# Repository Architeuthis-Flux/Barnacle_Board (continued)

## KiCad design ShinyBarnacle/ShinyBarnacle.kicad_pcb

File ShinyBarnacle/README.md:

# Shiny Barnacle

This one doesn't connect to the breadboard rows, just the RGBs. It mounts as a USB drive so you can drop a text file with colors to light the rows (or give it a sequence to step you through building a circuit.)

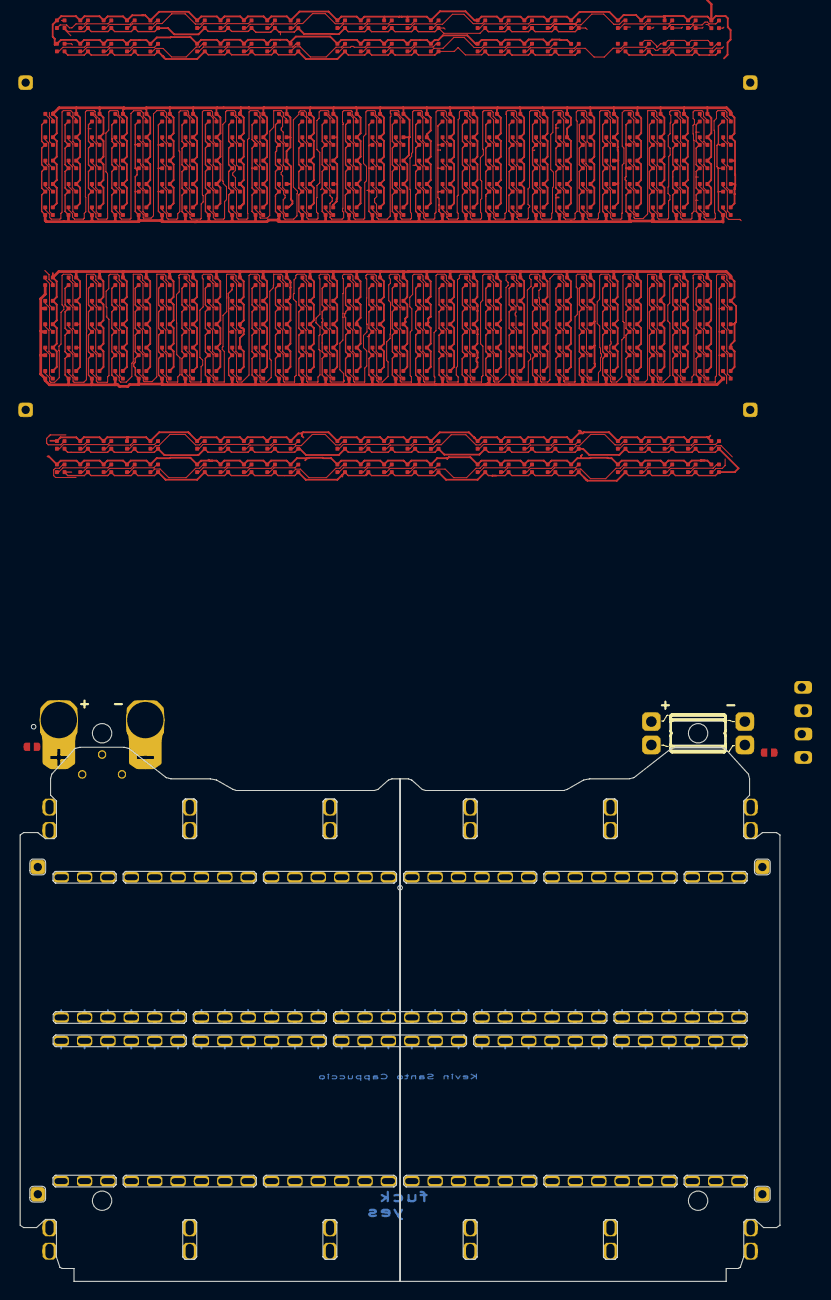
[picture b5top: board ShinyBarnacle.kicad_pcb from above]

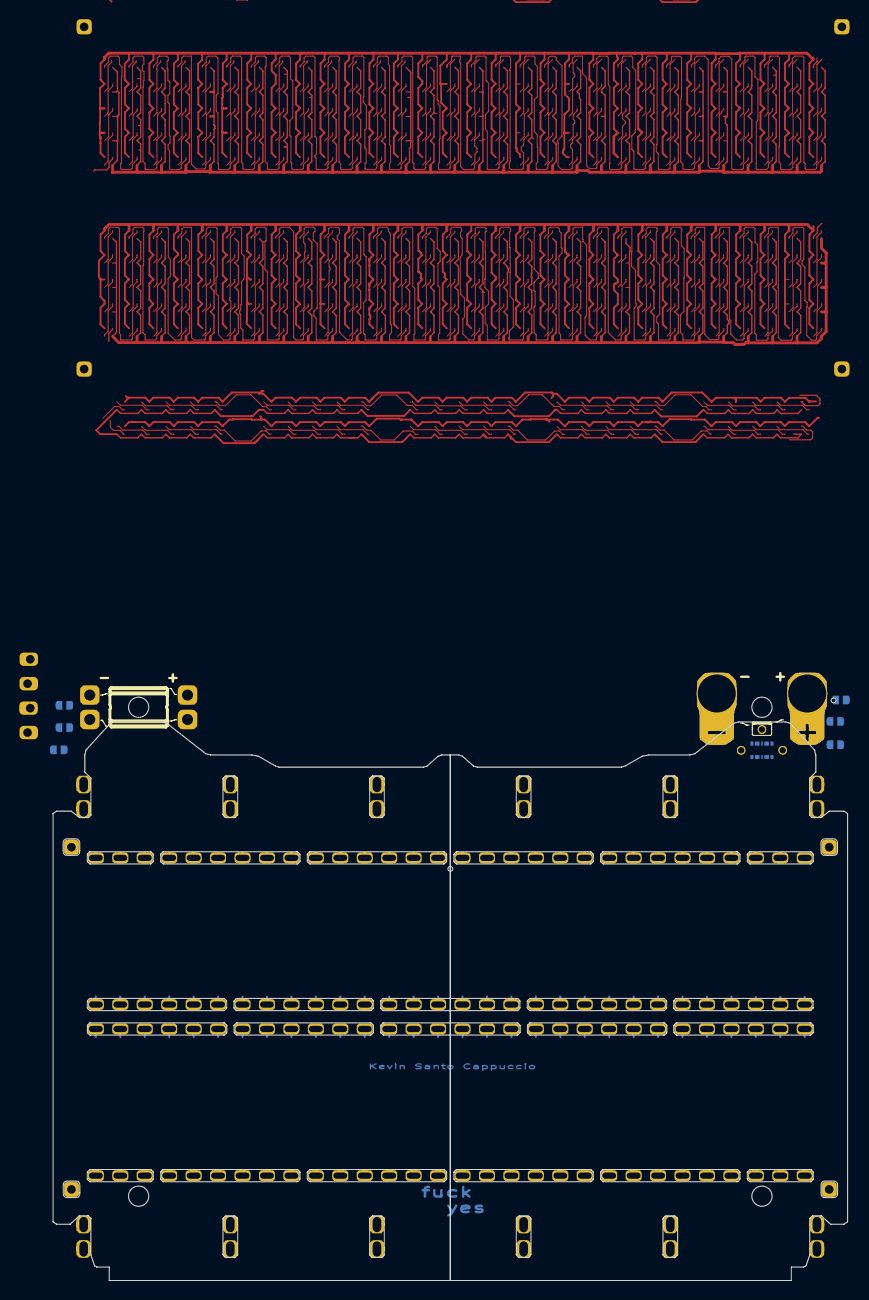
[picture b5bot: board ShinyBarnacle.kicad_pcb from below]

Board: 2 copper layers, 82.6 x 58.0 mm, 429 parts (9 on the bottom side), 409 nets.

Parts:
D1011, D1012, D1013, D1014, D1015, D1021, D1022, D1023, D1024, D1025, D1031, D1032, D1033, D1034, D1035, D1041, D1042, D1043, D1044, D1045, D1051, D1052, D1053, D1054, D1055, D1061, D1062, D1063, D1064, D1065, D1071, D1072, D1073, D1074, D1075, D1081, D1082, D1083, D1084, D1085, D1091, D1092, D1093, D1094, D1095, D1101, D1102, D1103, D1104, D1105, D1111, D1112, D1113, D1114, D1115, D1121, D1122, D1123, D1124, D1125, D1131, D1132, D1133, D1134, D1135, D1141, D1142, D1143, D1144, D1145, D1151, D1152, D1153, D1154, D1155, D1161, D1162, D1163, D1164, D1165, D1171, D1172, D1173, D1174, D1175, D1181, D1182, D1183, D1184, D1185, D1191, D1192, D1193, D1194, D1195, D1201, D1202, D1203, D1204, D1205, D1211, D1212, D1213, D1214, D1215, D1221, D1222, D1223, D1224, D1225, D1231, D1232, D1233, D1234, D1235, D1241, D1242, D1243, D1244, D1245, D1251, D1252, D1253, D1254, D1255, D1261, D1262, D1263, D1264, D1265, D1271, D1272, D1273, D1274, D1275, D1281, D1282, D1283, D1284, D1285, D1291, D1292, D1293, D1294, D1295, D1301, D1302, D1303, D1304, D1305, D1311, D1312, D1313, D1314, D1315, D1321, D1322, D1323, D1324, D1325, D1331, D1332, D1333, D1334, D1335, D1341, D1342, D1343, D1344, D1345, D1351, D1352, D1353, D1354, D1355, D1361, D1362, D1363, D1364, D1365, D1371, D1372, D1373, D1374, D1375, D1381, D1382, D1383, D1384, D1385, D1391, D1392, D1393, D1394, D1395, D1401, D1402, D1403, D1404, D1405, D1411, D1412, D1413, D1414, D1415, D1421, D1422, D1423, D1424, D1425, D1431, D1432, D1433, D1434, D1435, D1441, D1442, D1443, D1444, D1445, D1451, D1452, D1453, D1454, D1455, D1461, D1462, D1463, D1464, D1465, D1471, D1472, D1473, D1474, D1475, D1481, D1482, D1483, D1484, D1485, D1491, D1492, D1493, D1494, D1495, D1501, D1502, D1503, D1504, D1505, D1511, D1512, D1513, D1514, D1515, D1521, D1522, D1523, D1524, D1525, D1531, D1532, D1533, D1534, D1535, D1541, D1542, D1543, D1544, D1545, D1551, D1552, D1553, D1554, D1555, D1561, D1562, D1563, D1564, D1565, D1571, D1572, D1573, D1574, D1575, D1581, D1582, D1583, D1584, D1585, D1591, D1592, D1593, D1594, D1595, D1601, D1602, D1603, D1604, D1605, D1611, D1612, D1613, D1614, D1615, D1616, D1617, D1618, D1619, D1620, D1621, D1622, D1623, D1624, D1625, D1626, D1627, D1628, D1629, D1630, D1631, D1632, D1633, D1634, D1635, D1636, D1637, D1638, D1639, D1640, D1641, D1642, D1643, D1644, D1645, D1646, D1647, D1648, D1649, D1650, D1651, D1652, D1653, D1654, D1655, D1656, D1657, D1658, D1659, D1660, D1711, D1712, D1713, D1714, D1715, D1716, D1717, D1718, D1719, D1720, D1721, D1722, D1723, D1724, D1725, D1726, D1727, D1728, D1729, D1730, D1731, D1732, D1733, D1734, D1735, D1736, D1737, D1738, D1739, D1740, D1741, D1742, D1743, D1744, D1745, D1746, D1747, D1748, D1749, D1750, D1751, D1752, D1753, D1754, D1755, D1756, D1757, D1758, D1759, D1760: WS2812B; XL-1010RGBC-WS2812B
J1, J1#2: Conn_02x35_Top_Bottom; HEE70LP03BK_NumberedPads_CardGuide
J2: pad_sense_1; PinHeader_1x1_Smaller
J3: pad_sense_30; PinHeader_1x1_Smaller
J4: pad_sense_60; PinHeader_1x1_Smaller
J5: pad_sense_31; PinHeader_1x1_Smaller
J11: Connector_Breadboard; Breadboard_CustomClips_CorrectPins_2
J11#2: TopOutMAIN; PinHeader_1x1_Smaller
J12: TopInMAIN; PinHeader_1x1_Smaller
J13: BottomInMAIN; PinHeader_1x1_Smaller
J14: Conn_01x06; GT-B0353FSV06-02B0201
J15: BottomOutMAIN; PinHeader_1x1_Smaller
JP3, JP4, JP5, JP6, JP7, JP8, JP9, JP10: SolderJumper_2_Open; SolderJumper_2_Open_Small
TP16: LED DIN; PinHeader_1x1_0.6mm_tinyAF
TP18: LED 5V; PinHeader_1x1_0.6mm_tinyAF
TP19: LED GND; PinHeader_1x1_0.6mm_tinyAF
TP24: TOP_POS_RAIL; Pad_Clip_Banana_PlusSmaller_topBottom
TP25: TOP_POS_RAIL; PINHEADER_Larger_Pad
TP26: TOP_NEG_RAIL; Pad_Clip_Banana_MinusSmaller_topBottom
TP27: TOP_NEG_RAIL; PINHEADER_Larger_Pad
TP29: BOTTOM_POS_RAIL; PINHEADER_Larger_Pad
TP31: BOTTOM_NEG_RAIL; PINHEADER_Larger_Pad

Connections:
+5V: D1011.2 (VDD), D1012.2 (VDD), D1013.2 (VDD), D1014.2 (VDD), D1015.2 (VDD), D1021.2 (VDD), D1022.2 (VDD), D1023.2 (VDD), D1024.2 (VDD), D1025.2 (VDD), D1031.2 (VDD), D1032.2 (VDD), D1033.2 (VDD), D1034.2 (VDD), D1035.2 (VDD), D1041.2 (VDD), D1042.2 (VDD), D1043.2 (VDD), D1044.2 (VDD), D1045.2 (VDD), D1051.2 (VDD), D1052.2 (VDD), D1053.2 (VDD), D1054.2 (VDD), D1055.2 (VDD), D1061.2 (VDD), D1062.2 (VDD), D1063.2 (VDD), D1064.2 (VDD), D1065.2 (VDD), D1071.2 (VDD), D1072.2 (VDD), D1073.2 (VDD), D1074.2 (VDD), D1075.2 (VDD), D1081.2 (VDD), D1082.2 (VDD), D1083.2 (VDD), D1084.2 (VDD), D1085.2 (VDD), D1091.2 (VDD), D1092.2 (VDD), D1093.2 (VDD), D1094.2 (VDD), D1095.2 (VDD), D1101.2 (VDD), D1102.2 (VDD), D1103.2 (VDD), D1104.2 (VDD), D1105.2 (VDD), D1111.2 (VDD), D1112.2 (VDD), D1113.2 (VDD), D1114.2 (VDD), D1115.2 (VDD), D1121.2 (VDD), D1122.2 (VDD), D1123.2 (VDD), D1124.2 (VDD), D1125.2 (VDD), D1131.2 (VDD), D1132.2 (VDD), D1133.2 (VDD), D1134.2 (VDD), D1135.2 (VDD), D1141.2 (VDD), D1142.2 (VDD), D1143.2 (VDD), D1144.2 (VDD), D1145.2 (VDD), D1151.2 (VDD), D1152.2 (VDD), D1153.2 (VDD), D1154.2 (VDD), D1155.2 (VDD), D1161.2 (VDD), D1162.2 (VDD), D1163.2 (VDD), D1164.2 (VDD), D1165.2 (VDD), D1171.2 (VDD), D1172.2 (VDD), D1173.2 (VDD), D1174.2 (VDD), D1175.2 (VDD), D1181.2 (VDD), D1182.2 (VDD), D1183.2 (VDD), D1184.2 (VDD), D1185.2 (VDD), D1191.2 (VDD), D1192.2 (VDD), D1193.2 (VDD), D1194.2 (VDD), D1195.2 (VDD), D1201.2 (VDD), D1202.2 (VDD), D1203.2 (VDD), D1204.2 (VDD), D1205.2 (VDD), D1211.2 (VDD), D1212.2 (VDD), D1213.2 (VDD), D1214.2 (VDD), D1215.2 (VDD), D1221.2 (VDD), D1222.2 (VDD), D1223.2 (VDD), D1224.2 (VDD), D1225.2 (VDD), D1231.2 (VDD), D1232.2 (VDD), D1233.2 (VDD), D1234.2 (VDD), D1235.2 (VDD), D1241.2 (VDD), D1242.2 (VDD), D1243.2 (VDD), D1244.2 (VDD), D1245.2 (VDD), D1251.2 (VDD), D1252.2 (VDD), D1253.2 (VDD), D1254.2 (VDD), D1255.2 (VDD), D1261.2 (VDD), D1262.2 (VDD), D1263.2 (VDD), D1264.2 (VDD), D1265.2 (VDD), D1271.2 (VDD), D1272.2 (VDD), D1273.2 (VDD), D1274.2 (VDD), D1275.2 (VDD), D1281.2 (VDD), D1282.2 (VDD), D1283.2 (VDD), D1284.2 (VDD), D1285.2 (VDD), D1291.2 (VDD), D1292.2 (VDD), D1293.2 (VDD), D1294.2 (VDD), D1295.2 (VDD), D1301.2 (VDD), D1302.2 (VDD), D1303.2 (VDD), D1304.2 (VDD), D1305.2 (VDD), D1311.2 (VDD), D1312.2 (VDD), D1313.2 (VDD), D1314.2 (VDD), D1315.2 (VDD), D1321.2 (VDD), D1322.2 (VDD), D1323.2 (VDD), D1324.2 (VDD), D1325.2 (VDD), D1331.2 (VDD), D1332.2 (VDD), D1333.2 (VDD), D1334.2 (VDD), D1335.2 (VDD), D1341.2 (VDD), D1342.2 (VDD), D1343.2 (VDD), D1344.2 (VDD), D1345.2 (VDD), D1351.2 (VDD), D1352.2 (VDD), D1353.2 (VDD), D1354.2 (VDD), D1355.2 (VDD), D1361.2 (VDD), D1362.2 (VDD), D1363.2 (VDD), D1364.2 (VDD), D1365.2 (VDD), D1371.2 (VDD), D1372.2 (VDD), D1373.2 (VDD), D1374.2 (VDD), D1375.2 (VDD), D1381.2 (VDD), D1382.2 (VDD), D1383.2 (VDD), D1384.2 (VDD), D1385.2 (VDD), D1391.2 (VDD), D1392.2 (VDD), D1393.2 (VDD), D1394.2 (VDD), D1395.2 (VDD), D1401.2 (VDD), D1402.2 (VDD), D1403.2 (VDD), D1404.2 (VDD), D1405.2 (VDD), D1411.2 (VDD), D1412.2 (VDD), D1413.2 (VDD), D1414.2 (VDD), D1415.2 (VDD), D1421.2 (VDD), D1422.2 (VDD), D1423.2 (VDD), D1424.2 (VDD), D1425.2 (VDD), D1431.2 (VDD), D1432.2 (VDD), D1433.2 (VDD), D1434.2 (VDD), D1435.2 (VDD), D1441.2 (VDD), D1442.2 (VDD), D1443.2 (VDD), D1444.2 (VDD), D1445.2 (VDD), D1451.2 (VDD), D1452.2 (VDD), D1453.2 (VDD), D1454.2 (VDD), D1455.2 (VDD), D1461.2 (VDD), D1462.2 (VDD), D1463.2 (VDD), D1464.2 (VDD), D1465.2 (VDD), D1471.2 (VDD), D1472.2 (VDD), D1473.2 (VDD), D1474.2 (VDD), D1475.2 (VDD), D1481.2 (VDD), D1482.2 (VDD), D1483.2 (VDD), D1484.2 (VDD), D1485.2 (VDD), D1491.2 (VDD), D1492.2 (VDD), D1493.2 (VDD), D1494.2 (VDD), D1495.2 (VDD), D1501.2 (VDD), D1502.2 (VDD), D1503.2 (VDD), D1504.2 (VDD), D1505.2 (VDD), D1511.2 (VDD), D1512.2 (VDD), D1513.2 (VDD), D1514.2 (VDD), D1515.2 (VDD), D1521.2 (VDD), D1522.2 (VDD), D1523.2 (VDD), D1524.2 (VDD), D1525.2 (VDD), D1531.2 (VDD), D1532.2 (VDD), D1533.2 (VDD), D1534.2 (VDD), D1535.2 (VDD), D1541.2 (VDD), D1542.2 (VDD), D1543.2 (VDD), D1544.2 (VDD), D1545.2 (VDD), D1551.2 (VDD), D1552.2 (VDD), D1553.2 (VDD), D1554.2 (VDD), D1555.2 (VDD), D1561.2 (VDD), D1562.2 (VDD), D1563.2 (VDD), D1564.2 (VDD), D1565.2 (VDD), D1571.2 (VDD), D1572.2 (VDD), D1573.2 (VDD), D1574.2 (VDD), D1575.2 (VDD), D1581.2 (VDD), D1582.2 (VDD), D1583.2 (VDD), D1584.2 (VDD), D1585.2 (VDD), D1591.2 (VDD), D1592.2 (VDD), D1593.2 (VDD), D1594.2 (VDD), D1595.2 (VDD), D1601.2 (VDD), D1602.2 (VDD), D1603.2 (VDD), D1604.2 (VDD), D1605.2 (VDD), D1611.2 (VDD), D1612.2 (VDD), D1613.2 (VDD), D1614.2 (VDD), D1615.2 (VDD), D1616.2 (VDD), D1617.2 (VDD), D1618.2 (VDD), D1619.2 (VDD), D1620.2 (VDD), D1621.2 (VDD), D1622.2 (VDD), D1623.2 (VDD), D1624.2 (VDD), D1625.2 (VDD), D1626.2 (VDD), D1627.2 (VDD), D1628.2 (VDD), D1629.2 (VDD), D1630.2 (VDD), D1631.2 (VDD), D1632.2 (VDD), D1633.2 (VDD), D1634.2 (VDD), D1635.2 (VDD), D1636.2 (VDD), D1637.2 (VDD), D1638.2 (VDD), D1639.2 (VDD), D1640.2 (VDD), D1641.2 (VDD), D1642.2 (VDD), D1643.2 (VDD), D1644.2 (VDD), D1645.2 (VDD), D1646.2 (VDD), D1647.2 (VDD), D1648.2 (VDD), D1649.2 (VDD), D1650.2 (VDD), D1651.2 (VDD), D1652.2 (VDD), D1653.2 (VDD), D1654.2 (VDD), D1655.2 (VDD), D1656.2 (VDD), D1657.2 (VDD), D1658.2 (VDD), D1659.2 (VDD), D1660.2 (VDD), D1711.2 (VDD), D1712.2 (VDD), D1713.2 (VDD), D1714.2 (VDD), D1715.2 (VDD), D1716.2 (VDD), D1717.2 (VDD), D1718.2 (VDD), D1719.2 (VDD), D1720.2 (VDD), D1721.2 (VDD), D1722.2 (VDD), D1723.2 (VDD), D1724.2 (VDD), D1725.2 (VDD), D1726.2 (VDD), D1727.2 (VDD), D1728.2 (VDD), D1729.2 (VDD), D1730.2 (VDD), D1731.2 (VDD), D1732.2 (VDD), D1733.2 (VDD), D1734.2 (VDD), D1735.2 (VDD), D1736.2 (VDD), D1737.2 (VDD), D1738.2 (VDD), D1739.2 (VDD), D1740.2 (VDD), D1741.2 (VDD), D1742.2 (VDD), D1743.2 (VDD), D1744.2 (VDD), D1745.2 (VDD), D1746.2 (VDD), D1747.2 (VDD), D1748.2 (VDD), D1749.2 (VDD), D1750.2 (VDD), D1751.2 (VDD), D1752.2 (VDD), D1753.2 (VDD), D1754.2 (VDD), D1755.2 (VDD), D1756.2 (VDD), D1757.2 (VDD), D1758.2 (VDD), D1759.2 (VDD), D1760.2 (VDD)
BOT_RAIL_NEG: J11.64 (Bot_Neg), JP4.2 (B), JP8.2 (B), TP31.1
BOT_RAIL_POS: J11.63 (Bot_Pos), JP5.2 (B), JP9.2 (B), TP29.1
GND: D1011.3 (VSS), D1012.3 (VSS), D1013.3 (VSS), D1014.3 (VSS), D1015.3 (VSS), D1021.3 (VSS), D1022.3 (VSS), D1023.3 (VSS), D1024.3 (VSS), D1025.3 (VSS), D1031.3 (VSS), D1032.3 (VSS), D1033.3 (VSS), D1034.3 (VSS), D1035.3 (VSS), D1041.3 (VSS), D1042.3 (VSS), D1043.3 (VSS), D1044.3 (VSS), D1045.3 (VSS), D1051.3 (VSS), D1052.3 (VSS), D1053.3 (VSS), D1054.3 (VSS), D1055.3 (VSS), D1061.3 (VSS), D1062.3 (VSS), D1063.3 (VSS), D1064.3 (VSS), D1065.3 (VSS), D1071.3 (VSS), D1072.3 (VSS), D1073.3 (VSS), D1074.3 (VSS), D1075.3 (VSS), D1081.3 (VSS), D1082.3 (VSS), D1083.3 (VSS), D1084.3 (VSS), D1085.3 (VSS), D1091.3 (VSS), D1092.3 (VSS), D1093.3 (VSS), D1094.3 (VSS), D1095.3 (VSS), D1101.3 (VSS), D1102.3 (VSS), D1103.3 (VSS), D1104.3 (VSS), D1105.3 (VSS), D1111.3 (VSS), D1112.3 (VSS), D1113.3 (VSS), D1114.3 (VSS), D1115.3 (VSS), D1121.3 (VSS), D1122.3 (VSS), D1123.3 (VSS), D1124.3 (VSS), D1125.3 (VSS), D1131.3 (VSS), D1132.3 (VSS), D1133.3 (VSS), D1134.3 (VSS), D1135.3 (VSS), D1141.3 (VSS), D1142.3 (VSS), D1143.3 (VSS), D1144.3 (VSS), D1145.3 (VSS), D1151.3 (VSS), D1152.3 (VSS), D1153.3 (VSS), D1154.3 (VSS), D1155.3 (VSS), D1161.3 (VSS), D1162.3 (VSS), D1163.3 (VSS), D1164.3 (VSS), D1165.3 (VSS), D1171.3 (VSS), D1172.3 (VSS), D1173.3 (VSS), D1174.3 (VSS), D1175.3 (VSS), D1181.3 (VSS), D1182.3 (VSS), D1183.3 (VSS), D1184.3 (VSS), D1185.3 (VSS), D1191.3 (VSS), D1192.3 (VSS), D1193.3 (VSS), D1194.3 (VSS), D1195.3 (VSS), D1201.3 (VSS), D1202.3 (VSS), D1203.3 (VSS), D1204.3 (VSS), D1205.3 (VSS), D1211.3 (VSS), D1212.3 (VSS), D1213.3 (VSS), D1214.3 (VSS), D1215.3 (VSS), D1221.3 (VSS), D1222.3 (VSS), D1223.3 (VSS), D1224.3 (VSS), D1225.3 (VSS), D1231.3 (VSS), D1232.3 (VSS), D1233.3 (VSS), D1234.3 (VSS), D1235.3 (VSS), D1241.3 (VSS), D1242.3 (VSS), D1243.3 (VSS), D1244.3 (VSS), D1245.3 (VSS), D1251.3 (VSS), D1252.3 (VSS), D1253.3 (VSS), D1254.3 (VSS), D1255.3 (VSS), D1261.3 (VSS), D1262.3 (VSS), D1263.3 (VSS), D1264.3 (VSS), D1265.3 (VSS), D1271.3 (VSS), D1272.3 (VSS), D1273.3 (VSS), D1274.3 (VSS), D1275.3 (VSS), D1281.3 (VSS), D1282.3 (VSS), D1283.3 (VSS), D1284.3 (VSS), D1285.3 (VSS), D1291.3 (VSS), D1292.3 (VSS), D1293.3 (VSS), D1294.3 (VSS), D1295.3 (VSS), D1301.3 (VSS), D1302.3 (VSS), D1303.3 (VSS), D1304.3 (VSS), D1305.3 (VSS), D1311.3 (VSS), D1312.3 (VSS), D1313.3 (VSS), D1314.3 (VSS), D1315.3 (VSS), D1321.3 (VSS), D1322.3 (VSS), D1323.3 (VSS), D1324.3 (VSS), D1325.3 (VSS), D1331.3 (VSS), D1332.3 (VSS), D1333.3 (VSS), D1334.3 (VSS), D1335.3 (VSS), D1341.3 (VSS), D1342.3 (VSS), D1343.3 (VSS), D1344.3 (VSS), D1345.3 (VSS), D1351.3 (VSS), D1352.3 (VSS), D1353.3 (VSS), D1354.3 (VSS), D1355.3 (VSS), D1361.3 (VSS), D1362.3 (VSS), D1363.3 (VSS), D1364.3 (VSS), D1365.3 (VSS), D1371.3 (VSS), D1372.3 (VSS), D1373.3 (VSS), D1374.3 (VSS), D1375.3 (VSS), D1381.3 (VSS), D1382.3 (VSS), D1383.3 (VSS), D1384.3 (VSS), D1385.3 (VSS), D1391.3 (VSS), D1392.3 (VSS), D1393.3 (VSS), D1394.3 (VSS), D1395.3 (VSS), D1401.3 (VSS), D1402.3 (VSS), D1403.3 (VSS), D1404.3 (VSS), D1405.3 (VSS), D1411.3 (VSS), D1412.3 (VSS), D1413.3 (VSS), D1414.3 (VSS), D1415.3 (VSS), D1421.3 (VSS), D1422.3 (VSS), D1423.3 (VSS), D1424.3 (VSS), D1425.3 (VSS), D1431.3 (VSS), D1432.3 (VSS), D1433.3 (VSS), D1434.3 (VSS), D1435.3 (VSS), D1441.3 (VSS), D1442.3 (VSS), D1443.3 (VSS), D1444.3 (VSS), D1445.3 (VSS), D1451.3 (VSS), D1452.3 (VSS), D1453.3 (VSS), D1454.3 (VSS), D1455.3 (VSS), D1461.3 (VSS), D1462.3 (VSS), D1463.3 (VSS), D1464.3 (VSS), D1465.3 (VSS), D1471.3 (VSS), D1472.3 (VSS), D1473.3 (VSS), D1474.3 (VSS), D1475.3 (VSS), D1481.3 (VSS), D1482.3 (VSS), D1483.3 (VSS), D1484.3 (VSS), D1485.3 (VSS), D1491.3 (VSS), D1492.3 (VSS), D1493.3 (VSS), D1494.3 (VSS), D1495.3 (VSS), D1501.3 (VSS), D1502.3 (VSS), D1503.3 (VSS), D1504.3 (VSS), D1505.3 (VSS), D1511.3 (VSS), D1512.3 (VSS), D1513.3 (VSS), D1514.3 (VSS), D1515.3 (VSS), D1521.3 (VSS), D1522.3 (VSS), D1523.3 (VSS), D1524.3 (VSS), D1525.3 (VSS), D1531.3 (VSS), D1532.3 (VSS), D1533.3 (VSS), D1534.3 (VSS), D1535.3 (VSS), D1541.3 (VSS), D1542.3 (VSS), D1543.3 (VSS), D1544.3 (VSS), D1545.3 (VSS), D1551.3 (VSS), D1552.3 (VSS), D1553.3 (VSS), D1554.3 (VSS), D1555.3 (VSS), D1561.3 (VSS), D1562.3 (VSS), D1563.3 (VSS), D1564.3 (VSS), D1565.3 (VSS), D1571.3 (VSS), D1572.3 (VSS), D1573.3 (VSS), D1574.3 (VSS), D1575.3 (VSS), D1581.3 (VSS), D1582.3 (VSS), D1583.3 (VSS), D1584.3 (VSS), D1585.3 (VSS), D1591.3 (VSS), D1592.3 (VSS), D1593.3 (VSS), D1594.3 (VSS), D1595.3 (VSS), D1601.3 (VSS), D1602.3 (VSS), D1603.3 (VSS), D1604.3 (VSS), D1605.3 (VSS), D1611.3 (VSS), D1612.3 (VSS), D1613.3 (VSS), D1614.3 (VSS), D1615.3 (VSS), D1616.3 (VSS), D1617.3 (VSS), D1618.3 (VSS), D1619.3 (VSS), D1620.3 (VSS), D1621.3 (VSS), D1622.3 (VSS), D1623.3 (VSS), D1624.3 (VSS), D1625.3 (VSS), D1626.3 (VSS), D1627.3 (VSS), D1628.3 (VSS), D1629.3 (VSS), D1630.3 (VSS), D1631.3 (VSS), D1632.3 (VSS), D1633.3 (VSS), D1634.3 (VSS), D1635.3 (VSS), D1636.3 (VSS), D1637.3 (VSS), D1638.3 (VSS), D1639.3 (VSS), D1640.3 (VSS), D1641.3 (VSS), D1642.3 (VSS), D1643.3 (VSS), D1644.3 (VSS), D1645.3 (VSS), D1646.3 (VSS), D1647.3 (VSS), D1648.3 (VSS), D1649.3 (VSS), D1650.3 (VSS), D1651.3 (VSS), D1652.3 (VSS), D1653.3 (VSS), D1654.3 (VSS), D1655.3 (VSS), D1656.3 (VSS), D1657.3 (VSS), D1658.3 (VSS), D1659.3 (VSS), D1660.3 (VSS), D1711.3 (VSS), D1712.3 (VSS), D1713.3 (VSS), D1714.3 (VSS), D1715.3 (VSS), D1716.3 (VSS), D1717.3 (VSS), D1718.3 (VSS), D1719.3 (VSS), D1720.3 (VSS), D1721.3 (VSS), D1722.3 (VSS), D1723.3 (VSS), D1724.3 (VSS), D1725.3 (VSS), D1726.3 (VSS), D1727.3 (VSS), D1728.3 (VSS), D1729.3 (VSS), D1730.3 (VSS), D1731.3 (VSS), D1732.3 (VSS), D1733.3 (VSS), D1734.3 (VSS), D1735.3 (VSS), D1736.3 (VSS), D1737.3 (VSS), D1738.3 (VSS), D1739.3 (VSS), D1740.3 (VSS), D1741.3 (VSS), D1742.3 (VSS), D1743.3 (VSS), D1744.3 (VSS), D1745.3 (VSS), D1746.3 (VSS), D1747.3 (VSS), D1748.3 (VSS), D1749.3 (VSS), D1750.3 (VSS), D1751.3 (VSS), D1752.3 (VSS), D1753.3 (VSS), D1754.3 (VSS), D1755.3 (VSS), D1756.3 (VSS), D1757.3 (VSS), D1758.3 (VSS), D1759.3 (VSS), D1760.3 (VSS), J14.4, J14.5, TP19.1
LED_5V: J14.3, J14.6, TP18.1
LED_DAT: J14.1, J14.2, TP16.1
unnamed: D1011.1 (DOUT), D1012.4 (DIN)
unnamed: D1012.1 (DOUT), D1013.4 (DIN)
unnamed: D1013.1 (DOUT), D1014.4 (DIN)
unnamed: D1014.1 (DOUT), D1015.4 (DIN)
unnamed: D1015.1 (DOUT), D1021.4 (DIN)
unnamed: D1021.1 (DOUT), D1022.4 (DIN)
unnamed: D1022.1 (DOUT), D1023.4 (DIN)
unnamed: D1023.1 (DOUT), D1024.4 (DIN)
unnamed: D1024.1 (DOUT), D1025.4 (DIN)
unnamed: D1025.1 (DOUT), D1031.4 (DIN)
unnamed: D1031.1 (DOUT), D1032.4 (DIN)
unnamed: D1032.1 (DOUT), D1033.4 (DIN)
unnamed: D1033.1 (DOUT), D1034.4 (DIN)
unnamed: D1034.1 (DOUT), D1035.4 (DIN)
unnamed: D1035.1 (DOUT), D1041.4 (DIN)
unnamed: D1041.1 (DOUT), D1042.4 (DIN)
unnamed: D1042.1 (DOUT), D1043.4 (DIN)
unnamed: D1043.1 (DOUT), D1044.4 (DIN)
unnamed: D1044.1 (DOUT), D1045.4 (DIN)
unnamed: D1045.1 (DOUT), D1051.4 (DIN)
unnamed: D1051.1 (DOUT), D1052.4 (DIN)
unnamed: D1052.1 (DOUT), D1053.4 (DIN)
unnamed: D1053.1 (DOUT), D1054.4 (DIN)
unnamed: D1054.1 (DOUT), D1055.4 (DIN)
unnamed: D1055.1 (DOUT), D1061.4 (DIN)
unnamed: D1061.1 (DOUT), D1062.4 (DIN)
unnamed: D1062.1 (DOUT), D1063.4 (DIN)
unnamed: D1063.1 (DOUT), D1064.4 (DIN)
unnamed: D1064.1 (DOUT), D1065.4 (DIN)
unnamed: D1065.1 (DOUT), D1071.4 (DIN)
unnamed: D1071.1 (DOUT), D1072.4 (DIN)
unnamed: D1072.1 (DOUT), D1073.4 (DIN)
unnamed: D1073.1 (DOUT), D1074.4 (DIN)
unnamed: D1074.1 (DOUT), D1075.4 (DIN)
unnamed: D1075.1 (DOUT), D1081.4 (DIN)
unnamed: D1081.1 (DOUT), D1082.4 (DIN)
unnamed: D1082.1 (DOUT), D1083.4 (DIN)
unnamed: D1083.1 (DOUT), D1084.4 (DIN)
unnamed: D1084.1 (DOUT), D1085.4 (DIN)
unnamed: D1085.1 (DOUT), D1091.4 (DIN)
unnamed: D1091.1 (DOUT), D1092.4 (DIN)
unnamed: D1092.1 (DOUT), D1093.4 (DIN)
unnamed: D1093.1 (DOUT), D1094.4 (DIN)
unnamed: D1094.1 (DOUT), D1095.4 (DIN)
unnamed: D1095.1 (DOUT), D1101.4 (DIN)
unnamed: D1101.1 (DOUT), D1102.4 (DIN)
unnamed: D1102.1 (DOUT), D1103.4 (DIN)
unnamed: D1103.1 (DOUT), D1104.4 (DIN)
unnamed: D1104.1 (DOUT), D1105.4 (DIN)
unnamed: D1105.1 (DOUT), D1111.4 (DIN)
unnamed: D1111.1 (DOUT), D1112.4 (DIN)
unnamed: D1112.1 (DOUT), D1113.4 (DIN)
unnamed: D1113.1 (DOUT), D1114.4 (DIN)
unnamed: D1114.1 (DOUT), D1115.4 (DIN)
unnamed: D1115.1 (DOUT), D1121.4 (DIN)
unnamed: D1121.1 (DOUT), D1122.4 (DIN)
unnamed: D1122.1 (DOUT), D1123.4 (DIN)
unnamed: D1123.1 (DOUT), D1124.4 (DIN)
unnamed: D1124.1 (DOUT), D1125.4 (DIN)
unnamed: D1125.1 (DOUT), D1131.4 (DIN)
unnamed: D1131.1 (DOUT), D1132.4 (DIN)
unnamed: D1132.1 (DOUT), D1133.4 (DIN)
unnamed: D1133.1 (DOUT), D1134.4 (DIN)
unnamed: D1134.1 (DOUT), D1135.4 (DIN)
unnamed: D1135.1 (DOUT), D1141.4 (DIN)
unnamed: D1141.1 (DOUT), D1142.4 (DIN)
unnamed: D1142.1 (DOUT), D1143.4 (DIN)
unnamed: D1143.1 (DOUT), D1144.4 (DIN)
unnamed: D1144.1 (DOUT), D1145.4 (DIN)
unnamed: D1145.1 (DOUT), D1151.4 (DIN)
unnamed: D1151.1 (DOUT), D1152.4 (DIN)
unnamed: D1152.1 (DOUT), D1153.4 (DIN)
unnamed: D1153.1 (DOUT), D1154.4 (DIN)
unnamed: D1154.1 (DOUT), D1155.4 (DIN)
unnamed: D1155.1 (DOUT), D1161.4 (DIN)
unnamed: D1161.1 (DOUT), D1162.4 (DIN)
unnamed: D1162.1 (DOUT), D1163.4 (DIN)
unnamed: D1163.1 (DOUT), D1164.4 (DIN)
unnamed: D1164.1 (DOUT), D1165.4 (DIN)
unnamed: D1165.1 (DOUT), D1171.4 (DIN)
unnamed: D1171.1 (DOUT), D1172.4 (DIN)
unnamed: D1172.1 (DOUT), D1173.4 (DIN)
unnamed: D1173.1 (DOUT), D1174.4 (DIN)
unnamed: D1174.1 (DOUT), D1175.4 (DIN)
unnamed: D1175.1 (DOUT), D1181.4 (DIN)
unnamed: D1181.1 (DOUT), D1182.4 (DIN)
unnamed: D1182.1 (DOUT), D1183.4 (DIN)
unnamed: D1183.1 (DOUT), D1184.4 (DIN)
unnamed: D1184.1 (DOUT), D1185.4 (DIN)
unnamed: D1185.1 (DOUT), D1191.4 (DIN)
unnamed: D1191.1 (DOUT), D1192.4 (DIN)
unnamed: D1192.1 (DOUT), D1193.4 (DIN)
unnamed: D1193.1 (DOUT), D1194.4 (DIN)
unnamed: D1194.1 (DOUT), D1195.4 (DIN)
unnamed: D1195.1 (DOUT), D1201.4 (DIN)
unnamed: D1201.1 (DOUT), D1202.4 (DIN)
unnamed: D1202.1 (DOUT), D1203.4 (DIN)
unnamed: D1203.1 (DOUT), D1204.4 (DIN)
unnamed: D1204.1 (DOUT), D1205.4 (DIN)
unnamed: D1205.1 (DOUT), D1211.4 (DIN)
unnamed: D1211.1 (DOUT), D1212.4 (DIN)
unnamed: D1212.1 (DOUT), D1213.4 (DIN)
unnamed: D1213.1 (DOUT), D1214.4 (DIN)
unnamed: D1214.1 (DOUT), D1215.4 (DIN)
unnamed: D1215.1 (DOUT), D1221.4 (DIN)
unnamed: D1221.1 (DOUT), D1222.4 (DIN)
unnamed: D1222.1 (DOUT), D1223.4 (DIN)
unnamed: D1223.1 (DOUT), D1224.4 (DIN)
unnamed: D1224.1 (DOUT), D1225.4 (DIN)
unnamed: D1225.1 (DOUT), D1231.4 (DIN)
unnamed: D1231.1 (DOUT), D1232.4 (DIN)
unnamed: D1232.1 (DOUT), D1233.4 (DIN)
unnamed: D1233.1 (DOUT), D1234.4 (DIN)
unnamed: D1234.1 (DOUT), D1235.4 (DIN)
unnamed: D1235.1 (DOUT), D1241.4 (DIN)
unnamed: D1241.1 (DOUT), D1242.4 (DIN)
unnamed: D1242.1 (DOUT), D1243.4 (DIN)
unnamed: D1243.1 (DOUT), D1244.4 (DIN)
unnamed: D1244.1 (DOUT), D1245.4 (DIN)
unnamed: D1245.1 (DOUT), D1251.4 (DIN)
unnamed: D1251.1 (DOUT), D1252.4 (DIN)
unnamed: D1252.1 (DOUT), D1253.4 (DIN)
unnamed: D1253.1 (DOUT), D1254.4 (DIN)
unnamed: D1254.1 (DOUT), D1255.4 (DIN)
unnamed: D1255.1 (DOUT), D1261.4 (DIN)
unnamed: D1261.1 (DOUT), D1262.4 (DIN)
unnamed: D1262.1 (DOUT), D1263.4 (DIN)
unnamed: D1263.1 (DOUT), D1264.4 (DIN)
unnamed: D1264.1 (DOUT), D1265.4 (DIN)
unnamed: D1265.1 (DOUT), D1271.4 (DIN)
unnamed: D1271.1 (DOUT), D1272.4 (DIN)
unnamed: D1272.1 (DOUT), D1273.4 (DIN)
unnamed: D1273.1 (DOUT), D1274.4 (DIN)
unnamed: D1274.1 (DOUT), D1275.4 (DIN)
unnamed: D1275.1 (DOUT), D1281.4 (DIN)
unnamed: D1281.1 (DOUT), D1282.4 (DIN)
unnamed: D1282.1 (DOUT), D1283.4 (DIN)
unnamed: D1283.1 (DOUT), D1284.4 (DIN)
unnamed: D1284.1 (DOUT), D1285.4 (DIN)
unnamed: D1285.1 (DOUT), D1291.4 (DIN)
unnamed: D1291.1 (DOUT), D1292.4 (DIN)
unnamed: D1292.1 (DOUT), D1293.4 (DIN)
unnamed: D1293.1 (DOUT), D1294.4 (DIN)
unnamed: D1294.1 (DOUT), D1295.4 (DIN)
unnamed: D1295.1 (DOUT), D1301.4 (DIN)
unnamed: D1301.1 (DOUT), D1302.4 (DIN)
unnamed: D1302.1 (DOUT), D1303.4 (DIN)
unnamed: D1303.1 (DOUT), D1304.4 (DIN)
unnamed: D1304.1 (DOUT), D1305.4 (DIN)
unnamed: D1305.1 (DOUT), D1311.4 (DIN)
unnamed: D1311.1 (DOUT), D1312.4 (DIN)
unnamed: D1312.1 (DOUT), D1313.4 (DIN)
unnamed: D1313.1 (DOUT), D1314.4 (DIN)
unnamed: D1314.1 (DOUT), D1315.4 (DIN)
unnamed: D1315.1 (DOUT), D1321.4 (DIN)
unnamed: D1321.1 (DOUT), D1322.4 (DIN)
unnamed: D1322.1 (DOUT), D1323.4 (DIN)
unnamed: D1323.1 (DOUT), D1324.4 (DIN)
unnamed: D1324.1 (DOUT), D1325.4 (DIN)
unnamed: D1325.1 (DOUT), D1331.4 (DIN)
unnamed: D1331.1 (DOUT), D1332.4 (DIN)
unnamed: D1332.1 (DOUT), D1333.4 (DIN)
unnamed: D1333.1 (DOUT), D1334.4 (DIN)
unnamed: D1334.1 (DOUT), D1335.4 (DIN)
unnamed: D1335.1 (DOUT), D1341.4 (DIN)
unnamed: D1341.1 (DOUT), D1342.4 (DIN)
unnamed: D1342.1 (DOUT), D1343.4 (DIN)
unnamed: D1343.1 (DOUT), D1344.4 (DIN)
unnamed: D1344.1 (DOUT), D1345.4 (DIN)
unnamed: D1345.1 (DOUT), D1351.4 (DIN)
unnamed: D1351.1 (DOUT), D1352.4 (DIN)
unnamed: D1352.1 (DOUT), D1353.4 (DIN)
unnamed: D1353.1 (DOUT), D1354.4 (DIN)
unnamed: D1354.1 (DOUT), D1355.4 (DIN)
unnamed: D1355.1 (DOUT), D1361.4 (DIN)
unnamed: D1361.1 (DOUT), D1362.4 (DIN)
unnamed: D1362.1 (DOUT), D1363.4 (DIN)
unnamed: D1363.1 (DOUT), D1364.4 (DIN)
unnamed: D1364.1 (DOUT), D1365.4 (DIN)
unnamed: D1365.1 (DOUT), D1371.4 (DIN)
unnamed: D1371.1 (DOUT), D1372.4 (DIN)
unnamed: D1372.1 (DOUT), D1373.4 (DIN)
unnamed: D1373.1 (DOUT), D1374.4 (DIN)
unnamed: D1374.1 (DOUT), D1375.4 (DIN)
unnamed: D1375.1 (DOUT), D1381.4 (DIN)
unnamed: D1381.1 (DOUT), D1382.4 (DIN)
unnamed: D1382.1 (DOUT), D1383.4 (DIN)
unnamed: D1383.1 (DOUT), D1384.4 (DIN)
unnamed: D1384.1 (DOUT), D1385.4 (DIN)
unnamed: D1385.1 (DOUT), D1391.4 (DIN)
unnamed: D1391.1 (DOUT), D1392.4 (DIN)
unnamed: D1392.1 (DOUT), D1393.4 (DIN)
unnamed: D1393.1 (DOUT), D1394.4 (DIN)
unnamed: D1394.1 (DOUT), D1395.4 (DIN)
unnamed: D1395.1 (DOUT), D1401.4 (DIN)
unnamed: D1401.1 (DOUT), D1402.4 (DIN)
unnamed: D1402.1 (DOUT), D1403.4 (DIN)
unnamed: D1403.1 (DOUT), D1404.4 (DIN)
unnamed: D1404.1 (DOUT), D1405.4 (DIN)
unnamed: D1405.1 (DOUT), D1411.4 (DIN)
unnamed: D1411.1 (DOUT), D1412.4 (DIN)
unnamed: D1412.1 (DOUT), D1413.4 (DIN)
unnamed: D1413.1 (DOUT), D1414.4 (DIN)
unnamed: D1414.1 (DOUT), D1415.4 (DIN)
unnamed: D1415.1 (DOUT), D1421.4 (DIN)
unnamed: D1421.1 (DOUT), D1422.4 (DIN)
unnamed: D1422.1 (DOUT), D1423.4 (DIN)
unnamed: D1423.1 (DOUT), D1424.4 (DIN)
unnamed: D1424.1 (DOUT), D1425.4 (DIN)
unnamed: D1425.1 (DOUT), D1431.4 (DIN)
unnamed: D1431.1 (DOUT), D1432.4 (DIN)
unnamed: D1432.1 (DOUT), D1433.4 (DIN)
unnamed: D1433.1 (DOUT), D1434.4 (DIN)
unnamed: D1434.1 (DOUT), D1435.4 (DIN)
unnamed: D1435.1 (DOUT), D1441.4 (DIN)
unnamed: D1441.1 (DOUT), D1442.4 (DIN)
unnamed: D1442.1 (DOUT), D1443.4 (DIN)
unnamed: D1443.1 (DOUT), D1444.4 (DIN)
unnamed: D1444.1 (DOUT), D1445.4 (DIN)
unnamed: D1445.1 (DOUT), D1451.4 (DIN)
unnamed: D1451.1 (DOUT), D1452.4 (DIN)
unnamed: D1452.1 (DOUT), D1453.4 (DIN)
unnamed: D1453.1 (DOUT), D1454.4 (DIN)
unnamed: D1454.1 (DOUT), D1455.4 (DIN)
unnamed: D1455.1 (DOUT), D1461.4 (DIN)
unnamed: D1461.1 (DOUT), D1462.4 (DIN)
unnamed: D1462.1 (DOUT), D1463.4 (DIN)
unnamed: D1463.1 (DOUT), D1464.4 (DIN)
unnamed: D1464.1 (DOUT), D1465.4 (DIN)
unnamed: D1465.1 (DOUT), D1471.4 (DIN)
unnamed: D1471.1 (DOUT), D1472.4 (DIN)
unnamed: D1472.1 (DOUT), D1473.4 (DIN)
unnamed: D1473.1 (DOUT), D1474.4 (DIN)
unnamed: D1474.1 (DOUT), D1475.4 (DIN)
unnamed: D1475.1 (DOUT), D1481.4 (DIN)
unnamed: D1481.1 (DOUT), D1482.4 (DIN)
unnamed: D1482.1 (DOUT), D1483.4 (DIN)
unnamed: D1483.1 (DOUT), D1484.4 (DIN)
unnamed: D1484.1 (DOUT), D1485.4 (DIN)
unnamed: D1485.1 (DOUT), D1491.4 (DIN)
unnamed: D1491.1 (DOUT), D1492.4 (DIN)
unnamed: D1492.1 (DOUT), D1493.4 (DIN)
unnamed: D1493.1 (DOUT), D1494.4 (DIN)
unnamed: D1494.1 (DOUT), D1495.4 (DIN)
unnamed: D1495.1 (DOUT), D1501.4 (DIN)
unnamed: D1501.1 (DOUT), D1502.4 (DIN)
unnamed: D1502.1 (DOUT), D1503.4 (DIN)
unnamed: D1503.1 (DOUT), D1504.4 (DIN)
unnamed: D1504.1 (DOUT), D1505.4 (DIN)
unnamed: D1505.1 (DOUT), D1511.4 (DIN)
unnamed: D1511.1 (DOUT), D1512.4 (DIN)
unnamed: D1512.1 (DOUT), D1513.4 (DIN)
unnamed: D1513.1 (DOUT), D1514.4 (DIN)
unnamed: D1514.1 (DOUT), D1515.4 (DIN)
unnamed: D1515.1 (DOUT), D1521.4 (DIN)
unnamed: D1521.1 (DOUT), D1522.4 (DIN)
unnamed: D1522.1 (DOUT), D1523.4 (DIN)
unnamed: D1523.1 (DOUT), D1524.4 (DIN)
unnamed: D1524.1 (DOUT), D1525.4 (DIN)
unnamed: D1525.1 (DOUT), D1531.4 (DIN)
unnamed: D1531.1 (DOUT), D1532.4 (DIN)
unnamed: D1532.1 (DOUT), D1533.4 (DIN)
unnamed: D1533.1 (DOUT), D1534.4 (DIN)
unnamed: D1534.1 (DOUT), D1535.4 (DIN)
unnamed: D1535.1 (DOUT), D1541.4 (DIN)
unnamed: D1541.1 (DOUT), D1542.4 (DIN)
unnamed: D1542.1 (DOUT), D1543.4 (DIN)
unnamed: D1543.1 (DOUT), D1544.4 (DIN)
unnamed: D1544.1 (DOUT), D1545.4 (DIN)
unnamed: D1545.1 (DOUT), D1551.4 (DIN)
unnamed: D1551.1 (DOUT), D1552.4 (DIN)
unnamed: D1552.1 (DOUT), D1553.4 (DIN)
unnamed: D1553.1 (DOUT), D1554.4 (DIN)
unnamed: D1554.1 (DOUT), D1555.4 (DIN)
unnamed: D1555.1 (DOUT), D1561.4 (DIN)
unnamed: D1561.1 (DOUT), D1562.4 (DIN)
unnamed: D1562.1 (DOUT), D1563.4 (DIN)
unnamed: D1563.1 (DOUT), D1564.4 (DIN)
unnamed: D1564.1 (DOUT), D1565.4 (DIN)
unnamed: D1565.1 (DOUT), D1571.4 (DIN)
unnamed: D1571.1 (DOUT), D1572.4 (DIN)
unnamed: D1572.1 (DOUT), D1573.4 (DIN)
unnamed: D1573.1 (DOUT), D1574.4 (DIN)
unnamed: D1574.1 (DOUT), D1575.4 (DIN)
unnamed: D1575.1 (DOUT), D1581.4 (DIN)
unnamed: D1581.1 (DOUT), D1582.4 (DIN)
unnamed: D1582.1 (DOUT), D1583.4 (DIN)
unnamed: D1583.1 (DOUT), D1584.4 (DIN)
unnamed: D1584.1 (DOUT), D1585.4 (DIN)
unnamed: D1585.1 (DOUT), D1591.4 (DIN)
unnamed: D1591.1 (DOUT), D1592.4 (DIN)
unnamed: D1592.1 (DOUT), D1593.4 (DIN)
unnamed: D1593.1 (DOUT), D1594.4 (DIN)
unnamed: D1594.1 (DOUT), D1595.4 (DIN)
unnamed: D1595.1 (DOUT), D1601.4 (DIN)
unnamed: D1601.1 (DOUT), D1602.4 (DIN)
unnamed: D1602.1 (DOUT), D1603.4 (DIN)
unnamed: D1603.1 (DOUT), D1604.4 (DIN)
unnamed: D1604.1 (DOUT), D1605.4 (DIN)
unnamed: D1611.1 (DOUT), D1612.4 (DIN)
unnamed: D1612.1 (DOUT), D1613.4 (DIN)
unnamed: D1613.1 (DOUT), D1614.4 (DIN)
unnamed: D1614.1 (DOUT), D1615.4 (DIN)
unnamed: D1615.1 (DOUT), D1616.4 (DIN)
unnamed: D1616.1 (DOUT), D1617.4 (DIN)
unnamed: D1617.1 (DOUT), D1618.4 (DIN)
unnamed: D1618.1 (DOUT), D1619.4 (DIN)
unnamed: D1619.1 (DOUT), D1620.4 (DIN)
unnamed: D1620.1 (DOUT), D1621.4 (DIN)
unnamed: D1621.1 (DOUT), D1622.4 (DIN)
unnamed: D1622.1 (DOUT), D1623.4 (DIN)
unnamed: D1623.1 (DOUT), D1624.4 (DIN)
unnamed: D1624.1 (DOUT), D1625.4 (DIN)
unnamed: D1625.1 (DOUT), D1626.4 (DIN)
unnamed: D1626.1 (DOUT), D1627.4 (DIN)
unnamed: D1627.1 (DOUT), D1628.4 (DIN)
unnamed: D1628.1 (DOUT), D1629.4 (DIN)
unnamed: D1629.1 (DOUT), D1630.4 (DIN)
unnamed: D1630.1 (DOUT), D1631.4 (DIN)
unnamed: D1631.1 (DOUT), D1632.4 (DIN)
unnamed: D1632.1 (DOUT), D1633.4 (DIN)
unnamed: D1633.1 (DOUT), D1634.4 (DIN)
unnamed: D1634.1 (DOUT), D1635.4 (DIN)
unnamed: D1635.1 (DOUT), D1636.4 (DIN)
unnamed: D1636.1 (DOUT), D1637.4 (DIN)
unnamed: D1637.1 (DOUT), D1638.4 (DIN)
unnamed: D1638.1 (DOUT), D1639.4 (DIN)
unnamed: D1639.1 (DOUT), D1640.4 (DIN)
unnamed: D1640.1 (DOUT), D1641.4 (DIN)
unnamed: D1641.1 (DOUT), D1642.4 (DIN)
unnamed: D1642.1 (DOUT), D1643.4 (DIN)
unnamed: D1643.1 (DOUT), D1644.4 (DIN)
unnamed: D1644.1 (DOUT), D1645.4 (DIN)
unnamed: D1645.1 (DOUT), D1646.4 (DIN)
unnamed: D1646.1 (DOUT), D1647.4 (DIN)
unnamed: D1647.1 (DOUT), D1648.4 (DIN)
unnamed: D1648.1 (DOUT), D1649.4 (DIN)
unnamed: D1649.1 (DOUT), D1650.4 (DIN)
unnamed: D1650.1 (DOUT), D1651.4 (DIN)
unnamed: D1651.1 (DOUT), D1652.4 (DIN)
unnamed: D1652.1 (DOUT), D1653.4 (DIN)
unnamed: D1653.1 (DOUT), D1654.4 (DIN)
unnamed: D1654.1 (DOUT), D1655.4 (DIN)
unnamed: D1655.1 (DOUT), D1656.4 (DIN)
unnamed: D1656.1 (DOUT), D1657.4 (DIN)
unnamed: D1657.1 (DOUT), D1658.4 (DIN)
unnamed: D1658.1 (DOUT), D1659.4 (DIN)
unnamed: D1659.1 (DOUT), D1660.4 (DIN)
unnamed: D1660.1 (DOUT), D1711.4 (DIN)
unnamed: D1711.1 (DOUT), D1712.4 (DIN)
unnamed: D1712.1 (DOUT), D1713.4 (DIN)
unnamed: D1713.1 (DOUT), D1714.4 (DIN)
unnamed: D1714.1 (DOUT), D1715.4 (DIN)
unnamed: D1715.1 (DOUT), D1716.4 (DIN)
unnamed: D1716.1 (DOUT), D1717.4 (DIN)
unnamed: D1717.1 (DOUT), D1718.4 (DIN)
unnamed: D1718.1 (DOUT), D1719.4 (DIN)
unnamed: D1719.1 (DOUT), D1720.4 (DIN)
unnamed: D1720.1 (DOUT), D1721.4 (DIN)
unnamed: D1721.1 (DOUT), D1722.4 (DIN)
unnamed: D1722.1 (DOUT), D1723.4 (DIN)
unnamed: D1723.1 (DOUT), D1724.4 (DIN)
unnamed: D1724.1 (DOUT), D1725.4 (DIN)
unnamed: D1725.1 (DOUT), D1726.4 (DIN)
unnamed: D1726.1 (DOUT), D1727.4 (DIN)
unnamed: D1727.1 (DOUT), D1728.4 (DIN)
unnamed: D1728.1 (DOUT), D1729.4 (DIN)
unnamed: D1729.1 (DOUT), D1730.4 (DIN)
unnamed: D1730.1 (DOUT), D1731.4 (DIN)
unnamed: D1731.1 (DOUT), D1732.4 (DIN)
unnamed: D1732.1 (DOUT), D1733.4 (DIN)
unnamed: D1733.1 (DOUT), D1734.4 (DIN)
unnamed: D1734.1 (DOUT), D1735.4 (DIN)
unnamed: D1735.1 (DOUT), D1736.4 (DIN)
unnamed: D1736.1 (DOUT), D1737.4 (DIN)
unnamed: D1737.1 (DOUT), D1738.4 (DIN)
unnamed: D1738.1 (DOUT), D1739.4 (DIN)
unnamed: D1739.1 (DOUT), D1740.4 (DIN)
unnamed: D1740.1 (DOUT), D1741.4 (DIN)
unnamed: D1741.1 (DOUT), D1742.4 (DIN)
unnamed: D1742.1 (DOUT), D1743.4 (DIN)
unnamed: D1743.1 (DOUT), D1744.4 (DIN)
unnamed: D1744.1 (DOUT), D1745.4 (DIN)
unnamed: D1745.1 (DOUT), D1746.4 (DIN)
unnamed: D1746.1 (DOUT), D1747.4 (DIN)
unnamed: D1747.1 (DOUT), D1748.4 (DIN)
unnamed: D1748.1 (DOUT), D1749.4 (DIN)
unnamed: D1749.1 (DOUT), D1750.4 (DIN)
unnamed: D1750.1 (DOUT), D1751.4 (DIN)
unnamed: D1751.1 (DOUT), D1752.4 (DIN)
unnamed: D1752.1 (DOUT), D1753.4 (DIN)
unnamed: D1753.1 (DOUT), D1754.4 (DIN)
unnamed: D1754.1 (DOUT), D1755.4 (DIN)
unnamed: D1755.1 (DOUT), D1756.4 (DIN)
unnamed: D1756.1 (DOUT), D1757.4 (DIN)
unnamed: D1757.1 (DOUT), D1758.4 (DIN)
unnamed: D1758.1 (DOUT), D1759.4 (DIN)
unnamed: D1759.1 (DOUT), D1760.4 (DIN)
unnamed: J3.1, J5.1
unnamed: J12.1, J15.1, JP7.1 (A)
unnamed: J13.1, JP3.1 (A)
TOP_RAIL_NEG: J11.62 (Top_Neg), JP6.1 (A), JP10.1 (A), TP26.1, TP27.1
TOP_RAIL_POS: J11.61 (Top_Pos), JP3.2 (B), JP7.2 (B), TP24.1, TP25.1

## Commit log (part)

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2024-02-27 Added main board, proto, and sense barnacles
2024-02-27 Renamed stuff to fit the theme
2024-02-27 started routing
2024-02-27 add ADC resistors
2024-02-28 Finished routing
2024-02-28 Added silkscreen
2024-03-01 Started shinyBarnacle
2024-03-01 Finished the Shiny Barnacle
2024-03-02 Added the finished Shiny Barnacle Renders and stuff
2024-03-04 Added footprints
2024-03-05 Add spec for edge connector
2024-03-05 Add Edge Connector
2025-10-31 Messing around with a new version using the 5-hole spring clips
2026-03-05 The future is happening
2026-03-05 Update README for Barnacle Board Rev 2
    Expanded README with details about Barnacle Board Rev 2 features and images.
2026-03-05 Remove ws-4 image from README
2026-03-07 actually route most of the barnacles
2026-03-08 start smdBarnacle
2026-03-09 finish SMD barnacle
2026-03-10 Add images to README
    Added images to README for better visual representation.
2026-03-10 Remove duplicate image entries in README
    Removed duplicate images from the README file.
2026-03-17 addProtoSMD
